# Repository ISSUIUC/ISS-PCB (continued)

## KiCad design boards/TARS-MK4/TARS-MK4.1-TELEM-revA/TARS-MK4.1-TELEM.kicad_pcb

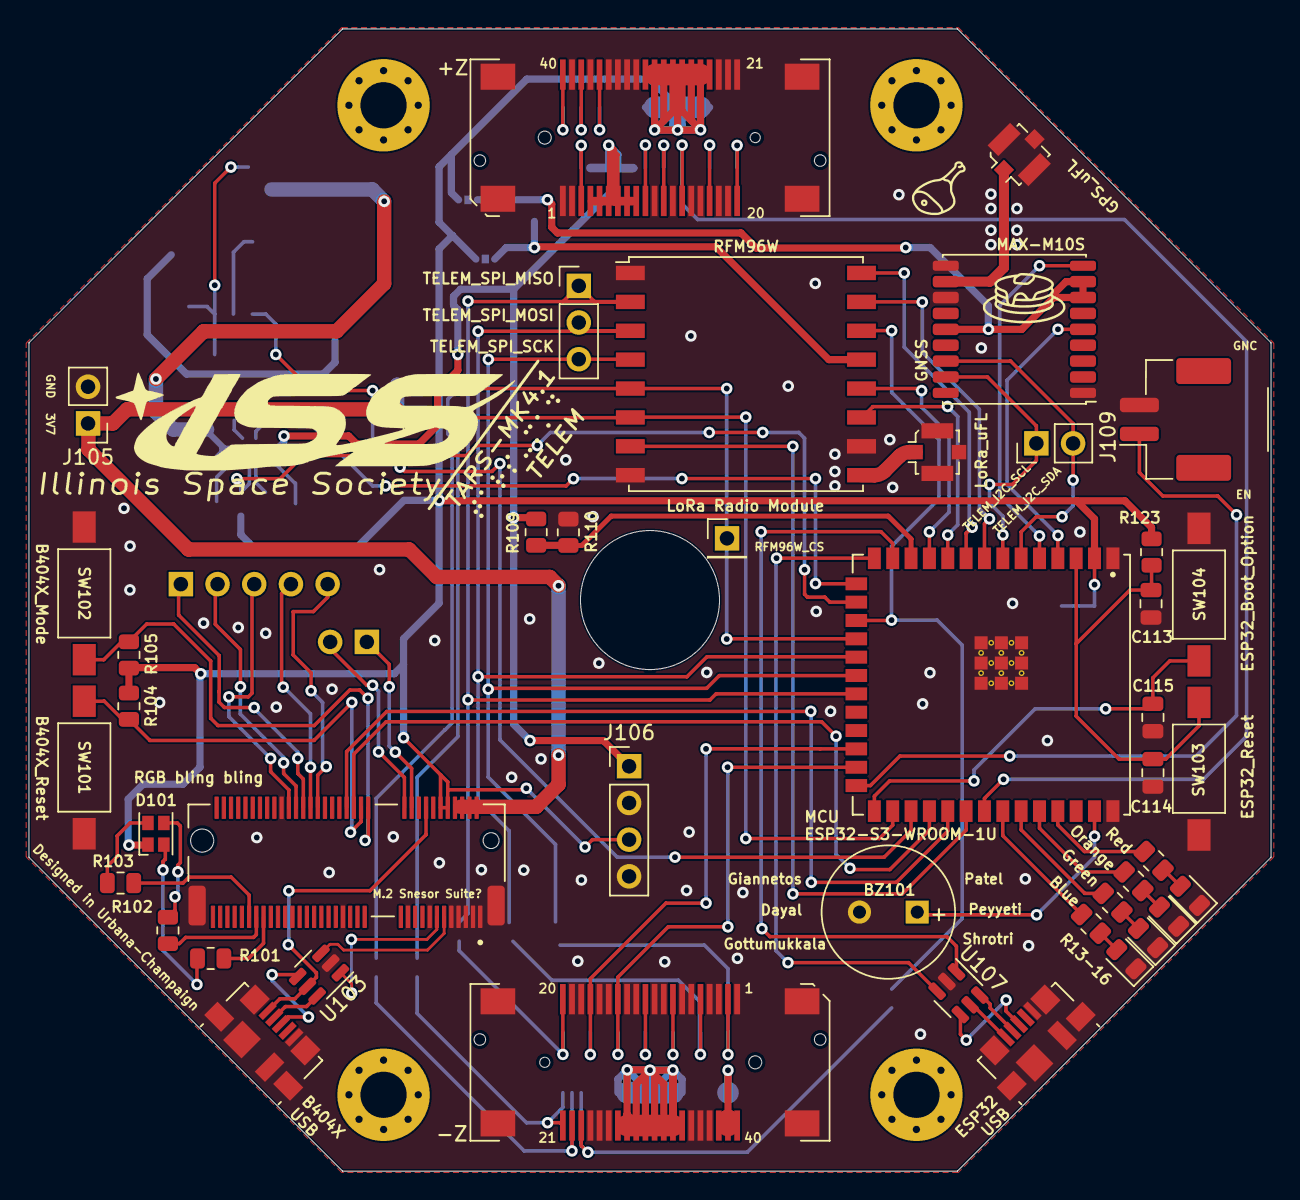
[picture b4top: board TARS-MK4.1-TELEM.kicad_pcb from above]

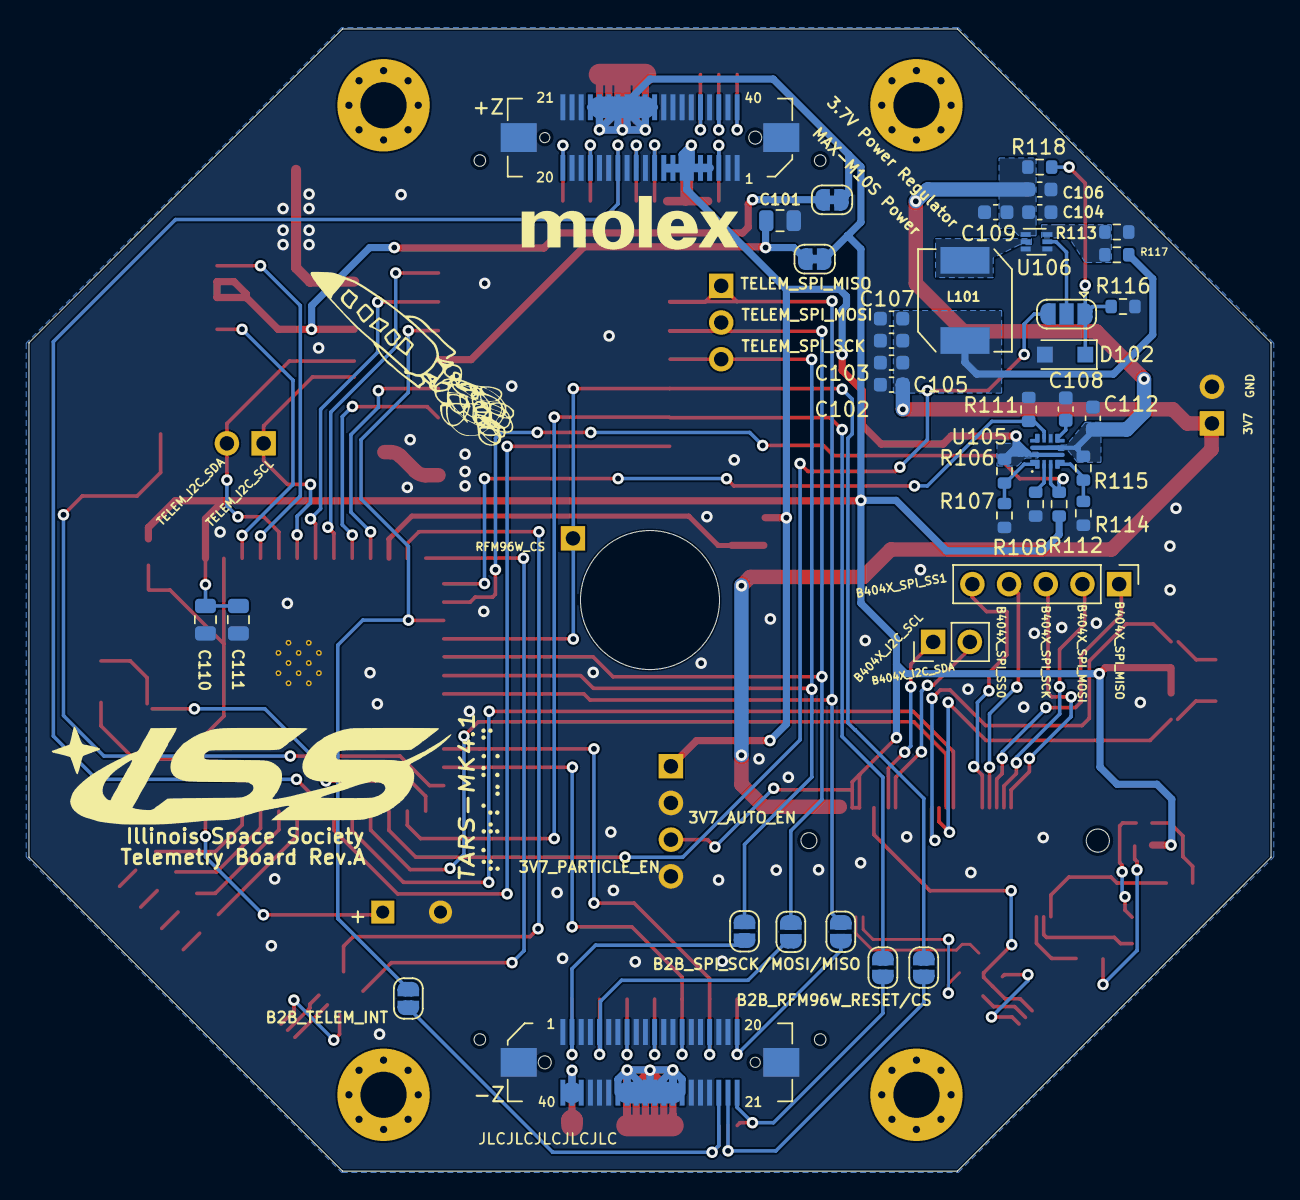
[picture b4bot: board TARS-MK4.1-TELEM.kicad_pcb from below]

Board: 2 copper layers, 86.0 x 79.1 mm, 83 parts (40 on the bottom side), 96 nets.

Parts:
BZ101: Buzzer; MagneticBuzzer_PUI_AT-0927-TT-6-R
C101: 10uF; C_0805_2012Metric
C102, C103, C105, C107: 22uF; C_0603_1608Metric
C104, C106: 10uF; C_0603_1608Metric
C108: 5.1nF; C_0603_1608Metric
C109: 0.1uF; C_0603_1608Metric
C110: 22uF; C_0805_2012Metric
C111, C114, C115: 0.1uF; C_0805_2012Metric
C112: 470uF; C_0603_1608Metric
C113: 1uF; C_0805_2012Metric
D101: LED_ABGR; LED_Cree-PLCC4_2x2mm_CW
D102: BZT52H-A5V1-QX; D_SOD-123F
D103: RED LED; LED_0805_2012Metric
D104: ORANGE LED; LED_0805_2012Metric
D105: GREEN LED; LED_0805_2012Metric
D106: BLUE LED; LED_0805_2012Metric
J101, J104: U.FL; U.FL_Molex_MCRF_73412-0110_Vertical
J102: B404X; TE_21992304
J103, J110: USB_B_Micro; USB_Micro-B_Molex_47346-0001
J105, J108, J114: Conn_01x02; PinHeader_1x02_P2.54mm_Vertical
J106: Conn_01x04; PinHeader_1x04_P2.54mm_Vertical
J107: Conn_01x04; PinHeader_1x05_P2.54mm_Vertical
J109: Molex Micro-Lock 5055780271; Molex_Micro-Lock_5055780271_1x02-1MP_P2.00mm_Horizontal
J111, J112: Molex_SlimStack_2091680401_2x20_P0.635mm; Molex_SlimStack_Receptacle_2091680401_2x20_P0.635mm
J113: Conn_01x03; PinHeader_1x03_P2.54mm_Vertical
J115: Conn_01x05; PinHeader_1x01_P2.54mm_Vertical
J116, J117: Molex_SlimStack_Plug_550910474_2x20_P0.365mm
JP101, JP102, JP103, JP104, JP105, JP108: SolderJumper_2_Open; SolderJumper-2_P1.3mm_Open_RoundedPad1.0x1.5mm
JP106, JP107: Jumper_NC_Small; SolderJumper-2_P1.3mm_Bridged_RoundedPad1.0x1.5mm
JP109: SolderJumper_3_Open; SolderJumper-3_P1.3mm_Open_RoundedPad1.0x1.5mm
L101: 2.2uH; L_TDK_SPM6530
R101, R102, R103: 1K; R_0805_2012Metric
R104, R105: 9K; R_0805_2012Metric
R106, R115: 470k; R_0603_1608Metric
R107, R114: 120k; R_0603_1608Metric
R108: 390k; R_0603_1608Metric
R109: 200k; R_0805_2012Metric
R110: 100k; R_0805_2012Metric
R111: 866; R_0603_1608Metric
R112: 47k; R_0603_1608Metric
R113, R116: 30k; R_0603_1608Metric
R117: 155k; R_0603_1608Metric
R118: 20k; R_0603_1608Metric
R119, R120, R121, R122: 470; R_0805_2012Metric
R123: 10K; R_0805_2012Metric
SW101, SW102, SW103, SW104: SW_Push; SW_SPST_FSMSM
U101: MAX-M10S; ublox_MAX
U102: RFM96W-433S2; HOPERF_RFM9XW_SMD
U103, U107: USBLC6-2SC6Y; SOT-23-6
U104: ESP32-S3-WROOM-1U
U105: TPS25947; VQFN-HR-RPW0010A
U106: TI_TPS566242DRLR; SOT-563

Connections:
/3V3: C110.1, C111.1, D101.1 (A), J102.10, J102.12, J106.3, J111.24, J111.25, J111.26, J111.27, J111.28, J111.29, J111.30, J111.31, J116.24, J116.25, J116.26, J116.27, J116.28, J116.29, J116.30, J116.31, JP106.1 (A), JP107.1 (A), R104.1, R105.1, R112.2, R123.2, U104.2 (3V3)
/3V7: C102.1, C103.1, C105.1, C107.1, J102.2, J102.4, J102.6, J102.8, J105.1, L101.1, R117.2
/3V7_PARTICLE_EN: JP109.3 (B), U104.29 (IO36)
/5V: J112.27, J112.28, J112.29, J112.30, J112.31, J112.32, J112.33, J112.34, J117.27, J117.28, J117.29, J117.30, J117.31, J117.32, J117.33, J117.34
/B2B_I2C_SCL: J112.11, J117.11
/B2B_I2C_SDA: J112.8, J117.8
/B2B_RFM96W_CS: J112.22, J117.22, JP102.1 (A)
/B2B_RFM96W_INT: J112.23, J117.23, JP108.2 (B)
/B2B_RFM96W_RESET: J112.21, J117.21, JP101.1 (A)
/B2B_SERVO_PWM: J111.3, J116.3
/B2B_SPI_MISO: J112.20, J117.20, JP103.1 (A)
/B2B_SPI_MOSI: J112.5, J117.5, JP104.1 (A)
/B2B_SPI_SCK: J112.2, J117.2, JP105.1 (A)
/B2B_UART_RX_PMB: J111.20, J116.20
/B2B_UART_RX_TELEM: J112.17, J117.17, U104.24 (IO47)
/B2B_UART_TX_PMB: J111.17, J116.17
/B2B_UART_TX_TELEM: J112.14, J117.14, U104.25 (IO48)
/B404X_I2C_SCL: J102.20, J108.1
/B404X_I2C_SDA: J102.22, J108.2
/B404X_Mode: J102.32, R105.2, SW102.2
/B404X_Reset: J102.34, R104.2, SW101.2
/B404X_SPI_MISO: J102.50, J107.1
/B404X_SPI_MOSI: J102.52, J107.2
/B404X_SPI_SCK: J102.54, J107.3
/B404X_SPI_SS0: J102.48, J107.4
/B404X_SPI_SS1: J102.46, J107.5
/CHIP_PU: C113.1, C114.2, R123.1, SW103.2, U104.3 (EN)
/ESP_USB_DN: U104.13 (IO19), U107.1 (I/O1)
/ESP_USB_DP: U104.14 (IO20), U107.3 (I/O2)
/GPIO_0: C115.2, SW104.2, U104.27 (IO0)
/ILM_3V7: R111.2, U104.15 (IO3), U105.9 (ILM)
/LED_BLUE: R122.1, U104.34 (IO41)
/LED_GREEN: R121.1, U104.35 (IO42)
/LED_ORANGE: R120.1, U104.36 (RXD0)
/LED_RED: R119.1, U104.37 (TXD0)
/LTE_USB_5V: J102.16, J103.1 (VBUS), U103.5 (VBUS)
/LTE_USB_DN: J102.13, U103.1 (I/O1)
/LTE_USB_DP: J102.11, U103.3 (I/O2)
/MAX-M10S_INT: U101.5 (EXTINT), U104.4 (IO4)
/MAX-M10S_RESET: U101.9 (RESET_N), U104.5 (IO5)
/PG_3V7: R112.1, U104.16 (IO46), U105.3 (PG/AUXOFF)
/PWM_BUZZER: BZ101.1 (-), U104.39 (IO1)
/RESERVED_1: J111.10, J116.10
/RESERVED_2: J111.12, J116.12
/RESERVED_3: J111.36, J116.36
/RESERVED_4: J111.38, J116.38
/RFM96W_CS: J115.1, JP102.2 (B), U102.5 (NSS), U104.18 (IO10)
/RFM96W_DIO1: U102.15 (DIO1), U104.8 (IO15)
/RFM96W_DIO2: U102.16 (DIO2), U104.9 (IO16)
/RFM96W_DIO3: U102.11 (DIO3), U104.10 (IO17)
/RFM96W_DIO4: U102.12 (DIO4), U104.11 (IO18)
/RFM96W_DIO5: U102.7 (DIO5), U104.32 (IO39)
/RFM96W_RESET: JP101.2 (B), U102.6 (RESET), U104.28 (IO35)
/RGB_B: J102.65, R103.1
/RGB_G: J102.63, R102.1
/RGB_R: J102.61, R101.1
/RTL_SDR_EN: J109.1, U104.26 (IO45)
/TEENSY_GPIO_1: J111.40, J116.40
/TEENSY_SWITCH: J111.14, J116.14, U104.33 (IO40)
/TELEM_I2C_SCL: J114.1, U101.17 (SCL), U104.7 (IO7)
/TELEM_I2C_SDA: J114.2, U101.16 (SDA), U104.6 (IO6)
/TELEM_INT: JP108.1 (A), U102.14 (DIO0), U104.17 (IO9)
/TELEM_SPI_MISO: J113.1, JP103.2 (B), U102.2 (MISO), U104.21 (IO13)
/TELEM_SPI_MOSI: J113.2, JP104.2 (B), U102.3 (MOSI), U104.19 (IO11)
/TELEM_SPI_SCK: J113.3, JP105.2 (B), U102.4 (SCK), U104.20 (IO12)
/Teensy_3V3: J112.38, J112.39, J112.40, J117.38, J117.39, J117.40
/UART_RX_PARTICLE: J102.38, U104.31 (IO38)
/UART_TX_PARTICLE: J102.36, U104.30 (IO37)
/VBAT: J106.1, J111.4, J111.5, J111.6, J111.7, J111.8, J111.9, J116.4, J116.5, J116.6, J116.7, J116.8, J116.9, R106.1, R109.1, U105.5 (IN)
/VBAT_3V7: C104.1, C106.1, C109.1, C112.1, R115.2, R118.2, U105.6 (OUT), U106.1 (VIN)
/VBAT_SENSE: R109.2, R110.1, U104.12 (IO8)
GND: BZ101.2 (+), C101.2, C102.2, C103.2, C104.2, C105.2, C106.2, C107.2, C108.2, C109.2, C110.2, C111.2, C112.2, C113.2, C114.1, C115.1, D102.2 (A), D103.1 (K), D104.1 (K), D105.1 (K), D106.1 (K), J101.2 (Ext), J102.1, J102.3, J102.5, J102.7, J102.9, J102.15, J102.21, J102.39, J102.56, J102.S1 (SHIELD), J103.5 (GND), J103.6 (Shield), J104.2 (Ext), J105.2, J106.2, J106.4, J109.2, J110.5 (GND), J110.6 (Shield), J111.1, J111.2, J111.11, J111.13, J111.15, J111.16, J111.18, J111.19, J111.21, J111.22, J111.23, J111.32, J111.33, J111.34, J111.35, J111.37, J111.39, J111.MP (MountPin), J112.1, J112.3, J112.4, J112.6, J112.7, J112.9, J112.10, J112.12, J112.13, J112.15, J112.16, J112.18, J112.19, J112.24, J112.25, J112.26, J112.35, J112.36, J112.37, J112.MP (MountPin), J116.1, J116.2, J116.11, J116.13, J116.15, J116.16, J116.18, J116.19, J116.21, J116.22, J116.23, J116.32, J116.33, J116.34, J116.35, J116.37, J116.39, J116.MP (MountPin), J117.1, J117.3, J117.4, J117.6, J117.7, J117.9, J117.10, J117.12, J117.13, J117.15, J117.16, J117.18, J117.19, J117.24, J117.25, J117.26, J117.35, J117.36, J117.37, J117.MP (MountPin), R107.2, R108.2, R110.2, R111.1, R113.2, R114.2, R116.2, SW101.1, SW102.1, SW103.1, SW104.1, U101.1 (GND), U101.10 (GND), U101.12 (GND), U102.1 (GND), U102.8 (GND), U102.10 (GND), U103.2 (GND), U104.1 (GND), U104.40 (GND), U104.41 (EPAD), U105.8 (GND), U106.3 (GND), U106.4 (AGND), U107.2 (GND)
unnamed: C101.1, JP106.2 (B), U102.13 (3.3V)
unnamed: C108.1, U105.7 (DVDT)
unnamed: D101.2 (BK), R103.2
unnamed: D101.3 (GK), R102.2
unnamed: D101.4 (RK), R101.2
unnamed: D102.1 (K), JP109.1 (A), R116.1, R118.1
unnamed: D103.2 (A), R119.2
unnamed: D104.2 (A), R120.2
unnamed: D105.2 (A), R121.2
unnamed: D106.2 (A), R122.2
unnamed: J101.1 (In), U101.11 (RF_IN)
unnamed: J103.2 (D-), U103.6 (I/O1)
unnamed: J103.3 (D+), U103.4 (I/O2)
unnamed: J104.1 (In), U102.9 (ANT)
unnamed: J110.1 (VBUS), U107.5 (VBUS)
unnamed: J110.2 (D-), U107.6 (I/O1)
unnamed: J110.3 (D+), U107.4 (I/O2)
unnamed: JP107.2 (B), U101.7 (V_IO), U101.8 (VCC), U101.14 (VCC_RF)
unnamed: JP109.2 (C), U106.5 (EN)
unnamed: L101.2, U106.2 (SW)
unnamed: R106.2, R107.1, U105.1 (EN/UVLO)
unnamed: R108.1, U105.2 (OVLO/OVCSEL)
unnamed: R113.1, R117.1, U106.6 (FB)
unnamed: R114.1, R115.1, U105.4 (PGTH/NFLT)

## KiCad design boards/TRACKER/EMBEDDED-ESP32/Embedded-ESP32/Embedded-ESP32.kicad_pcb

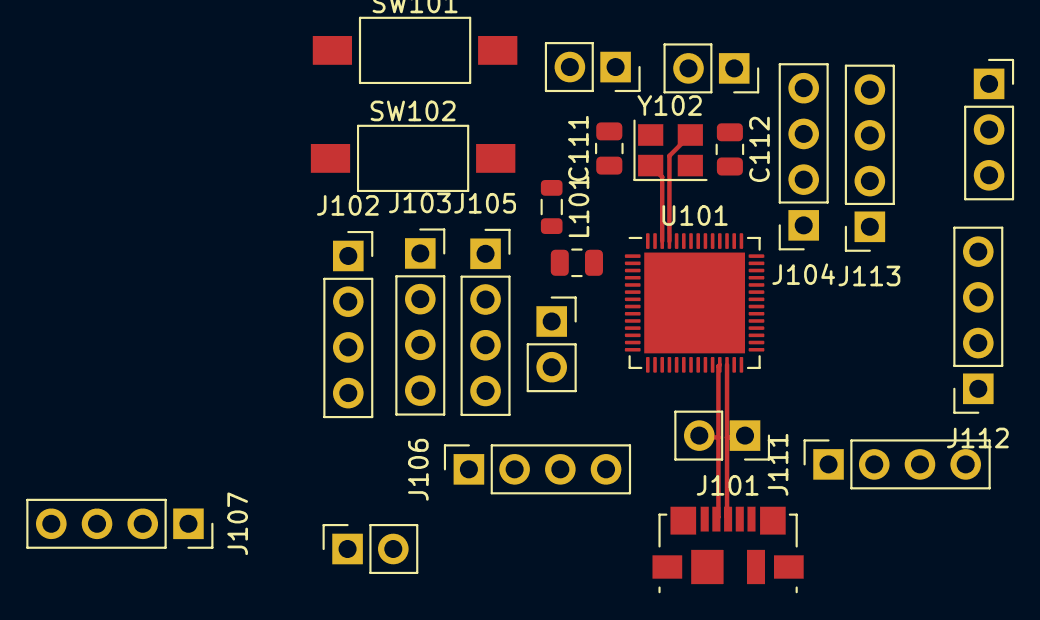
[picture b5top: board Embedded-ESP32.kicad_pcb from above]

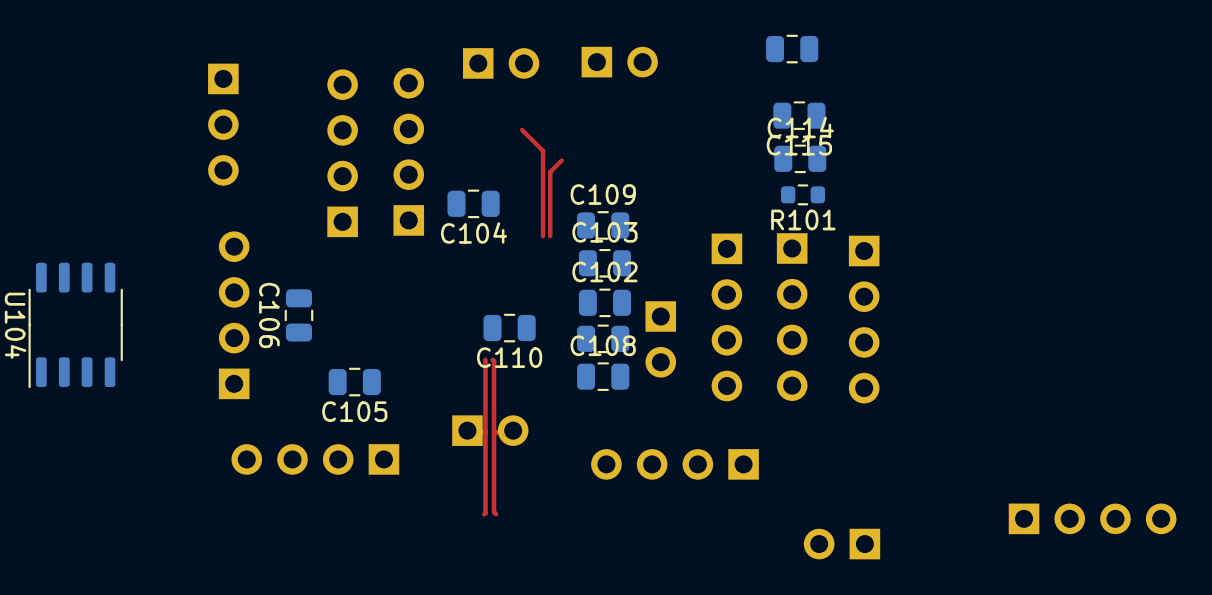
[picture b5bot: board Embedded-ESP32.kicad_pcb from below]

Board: 2 copper layers, 38 parts (14 on the bottom side), 53 nets.

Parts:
C101, C115: 1uF; C_0805_2012Metric
C102: 10nF; C_0805_2012Metric
C103, C104, C105, C106, C107, C108, C113, C114: 0.1uF; C_0805_2012Metric
C109, C110: 10uF; C_0805_2012Metric
C111, C112: TBD; C_0805_2012Metric
J101: USB_B_Micro; USB_Micro-B_Molex_47346-0001
J102, J103, J104, J105, J106, J107, J111, J112, J113: Conn_01x04; PinSocket_1x04_P2.54mm_Vertical
J108: Conn_01x03; PinSocket_1x03_P2.54mm_Vertical
J109, J110, J114, J115, J116: Conn_01x02; PinSocket_1x02_P2.54mm_Vertical
L101: L; L_0805_2012Metric
R101: 10K; R_0603_1608Metric
SW101, SW102: SW_Push; SW_SPST_FSMSM
U101: ESP32-S3; QFN-56-1EP_7x7mm_P0.4mm_EP5.6x5.6mm
U104: MX25L3233FM1; SOP-8_3.9x4.9mm_P1.27mm
Y102: Crystal_GND24; Crystal_SMD_Abracon_ABM8G-4Pin_3.2x2.5mm

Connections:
+3V3: C101.1, C102.1, C103.1, C104.1, C108.1, C109.1, C110.1, J116.2, L101.1, U101.20 (VDD3P3_RTC), U101.46 (VDD3P3_CPU), U101.55 (VDDA), U101.56 (VDDA)
/CHIP_PU: C114.2, C115.1, R101.1, SW102.2, U101.4 (CHIP_PU/RESET)
/CS: J111.4, U101.32 (SPICS0/GPIO29), U104.1 (~CS)
/GPIO_0: C113.2, J103.1, SW101.2, U101.5 (GPIO0/BOOT)
/HOLD: J111.2, U101.30 (SPIHD/GPIO27), U104.7 (~HOLD/SIO3)
/SCK: J112.1, U101.33 (SPICLK/GPIO30), U104.6 (SCLK)
/SPID: J112.3, U101.35 (SPID/GPIO32), U104.5 (SI/SIO0)
/SPIQ: J112.2, U101.34 (SPIQ/GPIO31), U104.2 (SO/SIO1)
/VDD_SPI: C105.1, C106.1, U101.29 (VDD_SPI), U104.8 (VCC)
/WP: J111.3, U101.31 (SPIWP/GPIO28), U104.3 (~WP/SIO2)
/X1: C111.1, U101.54 (XTAL_P), Y102.1
/X2: C112.1, U101.53 (XTAL_N), Y102.3
GND: C101.2, C102.2, C103.2, C104.2, C105.2, C106.2, C107.2, C108.2, C109.2, C110.2, C111.2, C112.2, C113.1, C114.1, C115.2, J101.5 (GND), J101.6 (Shield), J115.2, J116.1, SW101.1, SW102.1, U101.57 (GND), U104.4 (GND), Y102.2, Y102.4
unnamed: J101.3 (D+), J114.1, U101.26 (GPIO20/USB_D+/ADC2_CH9)
unnamed: J101.2 (D-), J114.2, U101.25 (GPIO19/USB_D-/ADC2_CH8)
unnamed: J102.1, U101.9 (GPIO4/ADC1_CH3)
unnamed: J102.2, U101.10 (GPIO5/ADC1_CH4)
unnamed: J102.3, U101.11 (GPIO6/ADC1_CH5)
unnamed: J102.4, U101.12 (GPIO7/ADC1_CH6)
unnamed: J103.2, U101.6 (GPIO1/ADC1_CH0)
unnamed: J103.3, U101.7 (GPIO2/ADC1_CH1)
unnamed: J103.4, U101.8 (GPIO3/ADC1_CH2)
unnamed: J104.1, U101.44 (MTCK/JTAG/GPIO39)
unnamed: J104.2, U101.45 (MTDO/JTAG/GPIO40)
unnamed: J104.3, U101.47 (MTDI/JTAG/GPIO41)
unnamed: J104.4, U101.48 (MTMS/JTAG/GPIO42)
unnamed: J105.1, U101.13 (GPIO8/ADC1_CH7)
unnamed: J105.2, U101.14 (GPIO9/ADC1_CH8)
unnamed: J105.3, U101.15 (GPIO10/ADC1_CH9)
unnamed: J105.4, U101.16 (GPIO11/ADC2_CH0)
unnamed: J106.1, U101.17 (GPIO12/ADC2_CH1)
unnamed: J106.2, U101.18 (GPIO13/ADC2_CH2)
unnamed: J106.3, U101.19 (GPIO14/ADC2_CH3)
unnamed: J106.4, U101.23 (GPIO17/ADC2_CH6)
unnamed: J107.1, U101.24 (GPIO18/ADC2_CH7)
unnamed: J107.2, U101.27 (GPIO21)
unnamed: J107.3, U101.43 (GPIO38)
unnamed: J107.4, U101.51 (GPIO45)
unnamed: J108.1, U101.52 (GPIO46)
unnamed: J108.2, U101.37 (SPICLK_P/GPIO47)
unnamed: J108.3, U101.36 (SPICLK_N/GPIO48)
unnamed: J109.1, U101.49 (U0TXD/PROG/GPIO43)
unnamed: J109.2, U101.50 (U0RXD/PROG/GPIO44)
unnamed: J110.1, U101.21 (GPIO15/ADC2_CH4/XTAL_32K_P)
unnamed: J110.2, U101.22 (GPIO16/ADC2_CH5/XTAL_32K_N)
unnamed: J111.1, U101.28 (SPI_CS1/GPIO26)
unnamed: J112.4, U101.38 (GPIO33)
unnamed: J113.1, U101.39 (GPIO34)
unnamed: J113.2, U101.40 (GPIO35)
unnamed: J113.3, U101.41 (GPIO36)
unnamed: J113.4, U101.42 (GPIO37)
unnamed: J115.1, U101.1 (LNA_IN/RF)
VDD3P3: C107.1, L101.2, U101.2 (VDD3P3), U101.3 (VDD3P3)

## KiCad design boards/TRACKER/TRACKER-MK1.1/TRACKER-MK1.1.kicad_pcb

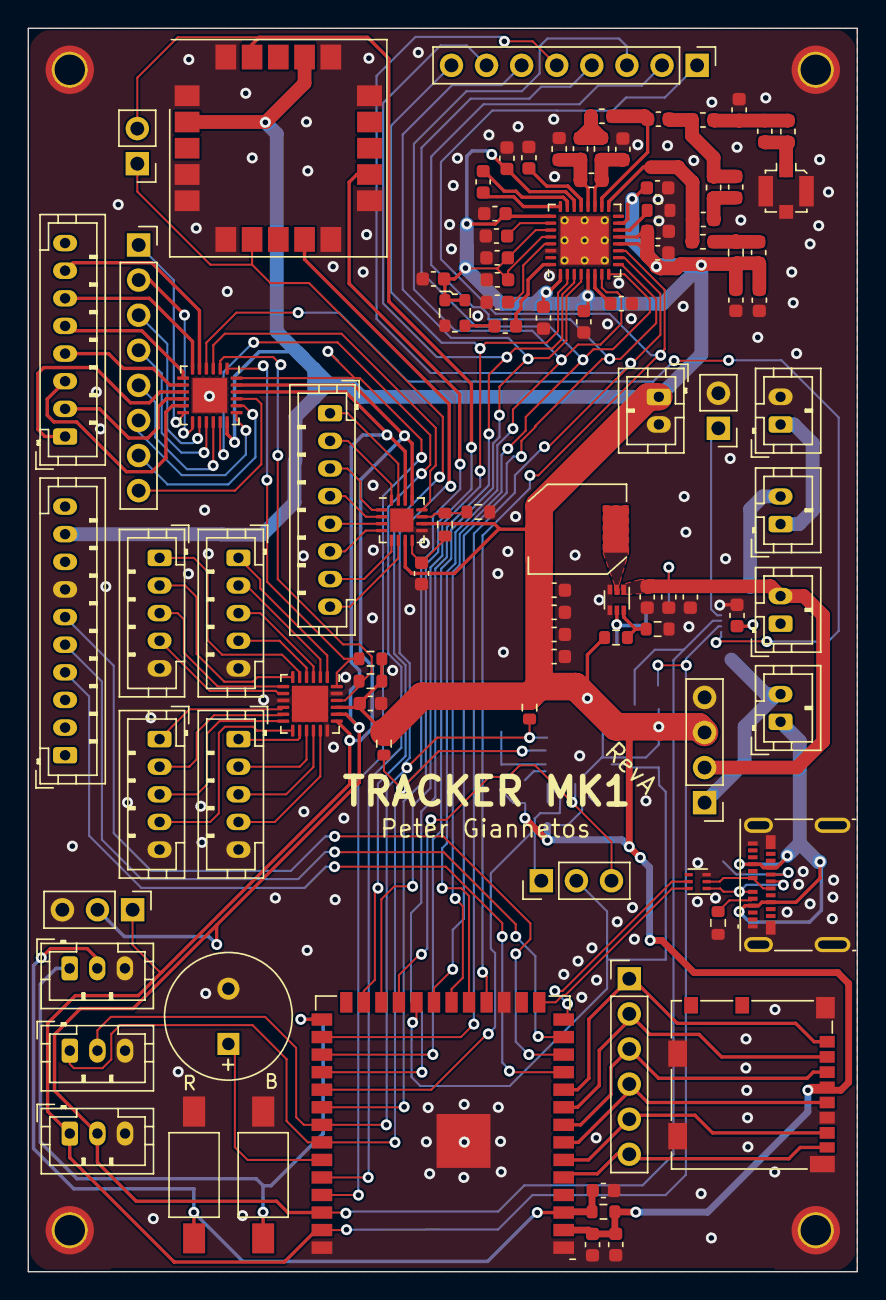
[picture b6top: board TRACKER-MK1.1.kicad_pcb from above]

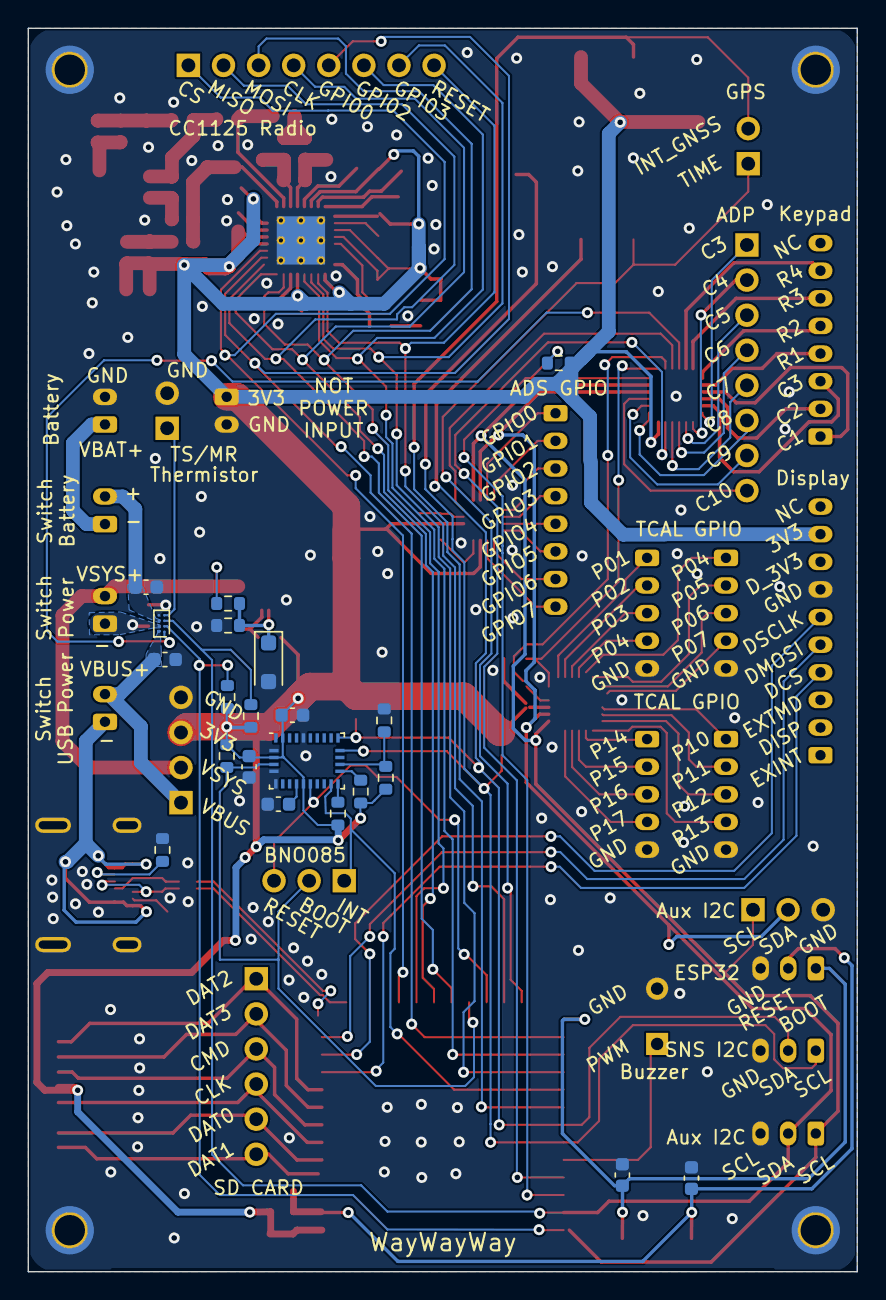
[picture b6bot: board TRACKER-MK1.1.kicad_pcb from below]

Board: 2 copper layers, 60.0 x 90.0 mm, 123 parts (21 on the bottom side), 117 nets.

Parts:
BT101: Battery; JST_PH_B2B-PH-K_1x02_P2.00mm_Vertical
BZ101: Buzzer; MagneticBuzzer_PUI_AT-0927-TT-6-R
C101, C103, C105, C118: 1uF; C_0603_1608Metric
C102, C108, C112, C115, C116, C117, C119, C120: 0.1uF; C_0603_1608Metric
C104, C106, C107: 10uF; C_0603_1608Metric
C109, C110, C111, C113, C114: 22uF; C_0603_1608Metric
C201: 100nF; C_0603_1608Metric
C202: 22pF; C_0603_1608Metric
C203: 1.8nF; C_0603_1608Metric
C204, C217: 10nF; C_0603_1608Metric
C205: 33pF; C_0603_1608Metric
C206: 100pF; C_0603_1608Metric
C207: 15pF; C_0603_1608Metric
C208, C210, C211, C214, C215, C218, C219, C220, C223, C224, C226: 47nF; C_0603_1608Metric
C209: 220nF; C_0603_1608Metric
C212, C222: 3.3pF; C_0603_1608Metric
C213: 1pF; C_0603_1608Metric
C216: 2.2pF; C_0603_1608Metric
C221: 3pF; C_0603_1608Metric
C225: TBD; C_0603_1608Metric
D101: BZT52H-A5V1-QX; D_SOD-123F
H101, H102, H103, H104: MountingHole_2.2mm_M2_ISO7380_Pad_TopBottom
J101: 1054500101; USB_C_Receptacle_Molex_105450-0101
J102: 1040310811; microSD_HC_Molex_104031-0811
J103, J104, J105, J106: JST-PH; JST_PH_B5B-PH-K_1x05_P2.00mm_Vertical
J107: JST-PH; JST_PH_B10B-PH-K_1x10_P2.00mm_Vertical
J108, J109: JST-PH; JST_PH_B8B-PH-K_1x08_P2.00mm_Vertical
J111: 2.54mm Pin Header; PinSocket_1x08_P2.54mm_Vertical
J112, J114, J115: JST-PH; JST_PH_B3B-PH-K_1x03_P2.00mm_Vertical
J113: JST-PH; JST_PH_B2B-PH-K_1x02_P2.00mm_Vertical
J116: U.FL; U.FL_Molex_MCRF_73412-0110_Vertical
J117: 2.54mm Pin Header; PinHeader_1x06_P2.54mm_Vertical
J120, J123: 2.54mm Pin Header; PinHeader_1x03_P2.54mm_Vertical
J121: 2.54mm Pin Header; PinHeader_1x02_P2.54mm_Vertical
J125: 2.54mm Pin Header; PinHeader_1x04_P2.54mm_Vertical
J126: 2.54mm Pin Header; PinHeader_1x08_P2.54mm_Vertical
L101: 2.2uH; L_TDK_SPM6530
L201: 10nH; L_0603_1608Metric
L202, L205, L207, L208: 12nH; L_0603_1608Metric
L203: 7.5nH; L_0603_1608Metric
L204: 15nH; L_0603_1608Metric
L206: 18nH; L_0603_1608Metric
R101, R102, R107, R114: 10k; R_0603_1608Metric
R103, R104: 5.1k; R_0603_1608Metric
R105: 100k; R_0603_1608Metric
R106, R112, R113: 0; R_0603_1608Metric
R108: 20k; R_0603_1608Metric
R109, R110: 30k; R_0603_1608Metric
R111: 135k; R_0603_1608Metric
R115, R116: 2.2k; R_0603_1608Metric
R117: 10K; R_0603_1608Metric
R118, R119, R120, R121: 3.3k; R_0603_1608Metric
R201: 56k; R_0603_1608Metric
R202: 10; R_0603_1608Metric
SW101: VBUS Switch; JST_PH_B2B-PH-K_1x02_P2.00mm_Vertical
SW102: Battery Switch; JST_PH_B2B-PH-K_1x02_P2.00mm_Vertical
SW103: Power Switch; JST_PH_B2B-PH-K_1x02_P2.00mm_Vertical
SW104, SW105: SW_Push; SW_SPST_FSMSM
TH101: B3950 NTC; PinHeader_1x02_P2.54mm_Vertical
U101: TCAL9539-Q1; WQFN-24-1EP_4x4mm_P0.5mm_EP2.6x2.6mm
U102: BQ25180; Texas_DSBGA-8_0.705x1.468mm_Layout2x4_P0.4mm
U103: ECMF02-2AMX6; ST_UQFN-6L_1.5x1.7mm_P0.5mm
U104: ADS7138-Q1; WQFN-16-1EP_3x3mm_P0.5mm_EP1.68x1.68mm
U105: ADP5589; LFCSP-24-1EP_4x4mm_P0.5mm_EP2.5x2.5mm
U106: TPS566242DRLR; SOT-563
U107: ESP32-S3-WROOM-1
U108: BNO085; LGA-28_5.2x3.8mm_P0.5mm
U109: SAM-M10Q-00B; uBlox_SAM-M10Q
U201: CC1125; VQFN-32-1EP_5x5mm_P0.5mm_EP3.5x3.5mm_ThermalVias
X201: ECS-TXO-2016MV-400-TR; Oscillator_SMD_ECS_2520MV-xxx-xx-4Pin_2.5x2.0mm

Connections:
/3V3: C102.1, C109.1, C110.1, C111.1, C112.1, C113.1, C114.1, C119.1, C120.1, C201.1, C204.1, C205.2, C206.1, C208.1, C211.1, C214.1, C215.1, C219.1, C220.1, C223.1, C224.1, C226.1, J102.4 (VDD), J107.9, J113.1, J125.3, L101.2, R101.1, R102.1, R107.1, R111.1, R112.2, R114.2, R115.2, R116.2, R117.2, R118.1, R119.1, R120.1, R121.1, R202.2, U101.21 (VCC), U104.7 (AVDD), U104.10 (DVDD), U105.18 (VDD), U107.2 (3V3), U108.3 (VDD), U108.10 (CLKSEL0), U108.28 (VDDIO), U109.2 (V_IO), U109.17 (VCC), U201.1 (VDD_GUARD), U201.5 (DVDD), U201.12 (DVDD), U201.13 (AVDD_IF), U201.15 (AVDD_RF), U201.22 (AVDD_SYNTH1), U201.25 (AVDD_PFD_CHP), U201.27 (AVDD_SYNTH2), U201.28 (AVDD_XOSC), X201.1 (Tri-State), X201.4 (VDD)
/ DISPLAY_CS: J107.4, U107.11 (IO18)
/ DISPLAY_MOSI: J107.5, U107.13 (IO19)
/ DISPLAY_SCLK: J107.6, U107.12 (IO8)
/ADC1_ALERT: U104.12 (ALERT), U105.3 (R5)
/ADC_DECAP: C105.1, R105.1, U104.8 (DECAP)
/ADP_~INT: R107.2, U105.24 (~INT), U107.37 (TXD0)
/ADP_~RESET: U105.17 (~RST), U107.36 (RXD0)
/BNO085_BOOT: J120.2, R114.1, U107.22 (IO14), U108.4 (BOOTN)
/BNO085_RESET: J120.3, U107.23 (IO21), U108.11 (NRST)
/BQ25180_INT: U102.A1 (INT), U105.4 (R4)
/CC1125_GPIO0: J126.5, U107.28 (IO35), U201.10 (GPIO0)
/CC1125_GPIO2: J126.6, U107.29 (IO36), U201.4 (GPIO2)
/CC1125_GPIO3: J126.7, U107.30 (IO37), U201.3 (GPIO3)
/CC1125_~RESET: J126.8, U107.24 (IO47), U201.2 (~RESET)
/CHIP_PU: C116.2, C118.1, J112.2, R117.1, SW105.2, U107.3 (EN)
/DN: J101.A7 (D-), J101.B7 (D-), U103.2 (D-_in)
/DP: J101.A6 (D+), J101.B6 (D+), U103.1 (D+_in)
/GPIO_0: C115.2, J112.1, SW104.2, U107.27 (IO0)
/I2C_AUX_SCL: J115.1, J123.1, R120.2, U101.19 (SCL), U102.B1 (SCL), U104.13 (SCL), U105.23 (SCL), U107.39 (IO1)
/I2C_AUX_SDA: J115.2, J123.2, R121.2, U101.20 (SDA), U102.C1 (SDA), U104.14 (SDA), U105.22 (SDA), U107.38 (IO2)
/I2C_SNS_SCL: J114.1, R119.2, U107.34 (IO41), U108.19 (H_SCL/SCK/RX), U109.12 (SCL)
/I2C_SNS_SDA: J114.2, R118.2, U107.33 (IO40), U108.20 (H_SDA/H_MISO/TX), U109.9 (SDA)
/INT_BNO085: J120.1, U107.31 (IO38), U108.14 (H_INTN)
/INT_GNSS: J121.2, U107.32 (IO39), U109.19 (EXTINT)
/KEYPAD_C1: J108.1, U105.9 (C0)
/KEYPAD_C2: J108.2, U105.10 (C1)
/KEYPAD_C3: J108.3, U105.11 (C2)
/KEYPAD_R1: J108.4, U105.8 (R0)
/KEYPAD_R2: J108.5, U105.7 (R1)
/KEYPAD_R3: J108.6, U105.6 (R2)
/KEYPAD_R4: J108.7, U105.5 (R3)
/PWM_BUZZER: BZ101.1 (-), U107.35 (IO42)
/Radio/ANT: C225.2, J116.1 (In), L208.2
/SD_CLK: J102.5 (CLK), J117.4, U107.7 (IO7)
/SD_CMD: J102.3 (CMD), J117.3, U107.8 (IO15)
/SD_DAT0: J102.7 (DAT0), J117.5, U107.6 (IO6)
/SD_DAT1: J102.8 (DAT1), J117.6, U107.5 (IO5)
/SD_DAT2: J102.1 (DAT2), J117.1, U107.10 (IO17)
/SD_DAT3: J102.2 (DAT3/CD), J117.2, U107.9 (IO16)
/SPI2_CC1125_~CS: J126.1, U107.18 (IO10), U201.11 (~CS)
/SPI2_RADIO_CLK: J126.4, U107.20 (IO12), U201.8 (SCLK)
/SPI2_RADIO_MISO: J126.2, U107.21 (IO13), U201.9 (SO(GPIO1))
/SPI2_RADIO_MOSI: J126.3, U107.19 (IO11), U201.7 (SI)
/TCAL_INT: R101.2, U101.22 (~INT), U105.2 (R6)
/TCAL_RESET: R102.2, U101.24 (~RESET), U105.1 (R7)
/TIME: J121.1, U107.25 (IO48), U109.7 (TIMEPULSE)
/TS/MR: TH101.1, U102.D1 (TS/MR)
/USB_ESP_DN: U103.5 (D-_out), U107.14 (IO20)
/USB_ESP_DP: U103.6 (D+_out), U107.15 (IO3)
/VBAT: C103.1, SW102.2 (B), U102.C2 (BAT)
/VBUS: C101.1, J125.1, SW101.2 (B), U102.A2 (IN)
/VSYS: C106.1, C107.1, C108.1, J125.2, R108.2, SW103.2 (B), U106.1 (VIN)
GND: BT101.2 (-), BZ101.2 (+), C101.2, C102.2, C103.2, C104.1, C105.2, C106.2, C107.2, C108.2, C109.2, C110.2, C111.2, C112.2, C113.2, C114.2, C115.1, C116.1, C117.2, C118.2, C119.2, C120.2, C201.2, C204.2, C206.2, C208.2, C209.2, C210.2, C211.2, C214.2, C215.2, C217.2, C218.2, C219.2, C220.2, C221.1, C222.1, C223.2, C224.2, C226.2, D101.2 (A), H101.1, H102.1, H103.1, H104.1, J101.A1 (GND), J101.A12 (GND), J101.B1 (GND), J101.B12 (GND), J101.S1 (SHIELD), J102.6 (VSS), J102.11 (SHIELD), J103.5, J104.5, J105.5, J106.5, J107.7, J112.3, J113.2, J114.3, J115.3, J116.2 (Ext), J123.3, J125.4, L202.1, R103.2, R104.2, R106.2, R109.2, R110.2, R113.1, R201.1, SW104.1, SW105.1, TH101.2, U101.9 (GND), U101.18 (A0), U101.23 (A1), U101.25 (GND), U102.D2 (GND), U103.3 (GND), U104.9 (GND), U104.17 (EPAD), U105.25 (GND), U106.3 (GND), U106.4 (AGND), U107.1 (GND), U107.17 (IO9), U107.40 (GND), U107.41 (EPAD), U108.2 (GND), U108.5 (PS1), U108.6 (PS0/WAKE), U108.25 (GNDIO), U109.1 (GND), U109.4 (GND), U109.5 (GND), U109.6 (GND), U109.10 (GND), U109.11 (GND), U109.15 (GND), U109.16 (GND), U109.20 (GND), U201.30 (XOSC_Q1), U201.33 (GND_EP), X201.2 (GND)
unnamed: BT101.1 (+), SW102.1 (A)
unnamed: C205.1, L201.2, R202.1
unnamed: C207.2, C213.1, L203.1
unnamed: C212.1, L205.2, L207.1
unnamed: C213.2, C216.1, L203.2, L206.1
unnamed: C221.2, C225.1, L206.2, L208.1
unnamed: D101.1 (K), R108.1, R109.1, U106.5 (EN)
unnamed: J101.A5 (CC1), R103.1
unnamed: J101.B5 (CC2), R104.1
unnamed: J103.1, U101.14
unnamed: J103.2, U101.15
unnamed: J103.3, U101.16
unnamed: J103.4, U101.17
unnamed: J104.1, U101.10
unnamed: J104.2, U101.11
unnamed: J104.3, U101.12
unnamed: J104.4, U101.13
unnamed: J105.1, U101.5 (P04)
unnamed: J105.2, U101.6 (P05)
unnamed: J105.3, U101.7 (P06)
unnamed: J105.4, U101.8 (P07)
unnamed: J106.1, U101.1 (P00)
unnamed: J106.2, U101.2 (P01)
unnamed: J106.3, U101.3 (P02)
unnamed: J106.4, U101.4 (P03)
unnamed: J109.1, U104.15 (AIN0/GPIO0)
unnamed: J109.2, U104.16 (AIN1/GPIO1)
unnamed: J109.3, U104.1 (ANI2/GPIO2)
unnamed: J109.4, U104.2 (AIN3/GPIO3)
unnamed: J109.5, U104.3 (AIN4/GPIO4)
unnamed: J109.6, U104.4 (AIN5/GPIO5)
unnamed: J109.7, U104.5 (AIN6/GPIO6)
unnamed: J109.8, U104.6 (AIN7/GPIO7)
unnamed: J111.1, U105.12 (C3)
unnamed: J111.2, U105.13 (C4)
unnamed: J111.3, U105.14 (C5)
unnamed: J111.4, U105.15 (C6)
unnamed: J111.5, U105.16 (C7)
unnamed: J111.6, U105.19 (C8)
unnamed: J111.7, U105.20 (C9)
unnamed: J111.8, U105.21 (C10)
unnamed: J101.A4 (VBUS), J101.A9 (VBUS), J101.B4 (VBUS), J101.B9 (VBUS), SW101.1 (A)
unnamed: C104.2, SW103.1 (A), U102.B2 (SYS)
unnamed: R105.2, R106.1, U104.11 (ADDR)
unnamed: R110.1, R111.2, U106.6 (FB)
unnamed: L101.1, U106.2 (SW)
unnamed: C117.1, U108.9 (CAP)
unnamed: R116.1, U108.15 (ENV_SCL)
unnamed: R115.1, U108.16 (ENV_SDA)
unnamed: R112.1, R113.2, U108.17 (H_SA0_MOSI)
unnamed: C209.1, U201.6 (DCPL)
unnamed: C210.1, U201.26 (DCPL_PFD_CHP)
unnamed: C217.1, U201.21 (DCPL_VCO)
unnamed: C218.1, U201.29 (DCPL_XOSC)
unnamed: C202.1, U201.32 (EXT_XOSC)
unnamed: C212.2, L202.2, L204.1, U201.20 (LNA_N)
unnamed: C222.2, L204.2, L207.2, U201.19 (LNA_P)
unnamed: C203.2, U201.23 (LPF0)
unnamed: C203.1, U201.24 (LPF1)
unnamed: C207.1, L201.1, U201.17 (PA)
unnamed: R201.2, U201.14 (RBIAS)
unnamed: C216.2, L205.1, U201.18 (TRX_SW)
unnamed: C202.2, X201.3 (OUT)

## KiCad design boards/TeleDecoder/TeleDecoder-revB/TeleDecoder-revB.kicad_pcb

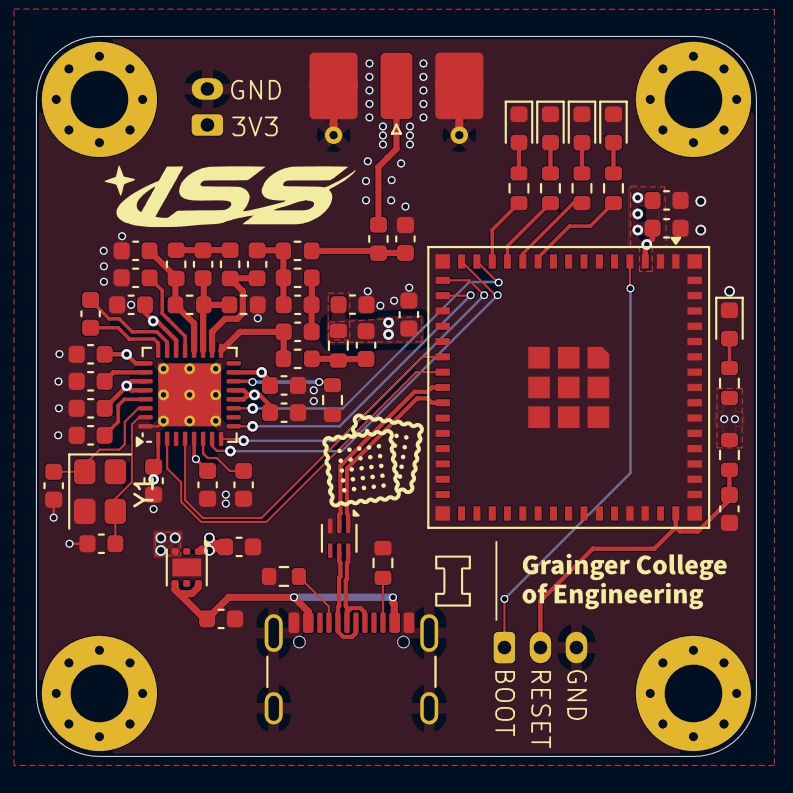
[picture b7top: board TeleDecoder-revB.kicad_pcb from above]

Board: 4 copper layers, 40.0 x 40.0 mm, 64 parts (0 on the bottom side), 45 nets.

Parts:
C1, C2, C127: 1uF; C_0603_1608Metric
C101: 22uF; C_0603_1608Metric
C102: 100nF; C_0603_1608Metric
C103, C119: 10nF; C_0603_1608Metric
C104: 56pF; C_0603_1608Metric
C105: 100pF; C_0603_1608Metric
C106: 39pF; C_0603_1608Metric
C107: 2.2pF; C_0603_1608Metric
C108, C109: 10pF; C_0603_1608Metric
C110, C111, C113: 5.1pF; C_0603_1608Metric
C112: 1.8nF; C_0603_1608Metric
C114: 6.2pF; C_0603_1608Metric
C115, C117, C118, C120, C121, C122, C123, C124, C125: 47nF; C_0603_1608Metric
C116: 220nF; C_0603_1608Metric
D101, D105: LED_RED; LED_0603_1608Metric
D102: LED_BLUE; LED_0603_1608Metric
D103: LED_GREEN; LED_0603_1608Metric
D104: LED_ORANGE; LED_0603_1608Metric
H101, H102, H103, H104: MountingHole; MountingHole_3.2mm_M3_Pad_Via
J101: Conn_01x03; JST_PH_B3B-PH-K_1x03_P2.00mm_Vertical
J102: USB4105-GF-A; USB_C_Receptacle_GCT_USB4105-xx-A_16P_TopMnt_Horizontal
J103: Conn_01x02; JST_PH_B2B-PH-K_1x02_P2.00mm_Vertical
J104: Conn_Coaxial; SMA_Molex_73251-2120_EdgeMount_Horizontal
L101, L102: 56nH; L_0603_1608Metric
L103, L106: 15nH; L_0603_1608Metric
L104, L105: 27nH; L_0603_1608Metric
L107: 43nH; L_0603_1608Metric
L108: 22nH; L_0603_1608Metric
R101, R102: 5.1k; R_0603_1608Metric
R103: 18; R_0603_1608Metric
R104: 56k; R_0603_1608Metric
R105, R106, R107, R108, R110: 470; R_0603_1608Metric
R109: 20k; R_0603_1608Metric
U101: ESP32-S3-MINI-1U; ESP32-S2-MINI-1U
U102: ECMF02-2AMX6; ST_UQFN-6L_1.5x1.7mm_P0.5mm
U103: CC1120; VQFN-32-1EP_5x5mm_P0.5mm_EP3.5x3.5mm_ThermalVias
U104: TPS746-Q1; WSON-6-1EP_2x2mm_P0.65mm_EP1x1.6mm
Y1: NDK NX3225SA; Crystal_SMD_3225-4Pin_3.2x2.5mm

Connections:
+3V3: C2.1, C101.1, C102.1, C103.1, C104.2, C105.1, C115.1, C117.1, C118.1, C120.1, C121.1, C123.1, C124.1, J103.1, R103.2, R109.2, R110.1, U101.3 (3V3), U103.1 (VDD_GUARD), U103.5 (DVDD), U103.12 (DVDD), U103.13 (AVDD_IF), U103.15 (AVDD_RF), U103.22 (AVDD_SYNTH1), U103.25 (AVDD_PFD_CHP), U103.27 (AVDD_SYNTH2), U103.28 (AVDD_XOSC), U104.1 (OUT)
+5V: C1.1, J102.A4 (VBUS), J102.A9 (VBUS), J102.B4 (VBUS), J102.B9 (VBUS), U104.4 (EN), U104.6 (IN)
/BOOT: J101.1, U101.4 (IO0)
/CS_RADIO: U101.14 (IO10), U103.11 (~CS)
/D+: J102.A6 (D+), J102.B6 (D+), U102.6 (D+_out)
/D-: J102.A7 (D-), J102.B7 (D-), U102.5 (D-_out)
/LED_BLUE: R106.1, U101.13 (IO9)
/LED_GREEN: R107.1, U101.12 (IO8)
/LED_ORANGE: R108.1, U101.11 (IO7)
/LED_RED: R105.1, U101.10 (IO6)
/LNA_N: C111.1, L102.2, L105.1, U103.20 (LNA_N)
/LNA_P: C110.1, L102.1, L104.1, U103.19 (LNA_P)
/MISO0: U101.17 (IO13), U103.9 (SO(GPIO1))
/MOSI0: U101.15 (IO11), U103.7 (SI)
/PA: C106.1, L101.1, U103.17 (PA)
/RADIO_INT: U101.21 (IO17), U103.4 (GPIO2)
/RESET: C127.1, J101.2, R109.1, U101.45 (EN)
/RESET_IN: U101.22 (IO18), U103.2 (~RESET)
/SCLK0: U101.16 (IO12), U103.8 (SCLK)
/TRX_SW: C113.1, L106.1, U103.18 (TRX_SW)
/USB_D+: U101.24 (USB_D+), U102.1 (D+_in)
/USB_D-: U101.23 (USB_D-), U102.2 (D-_in)
GND: C1.2, C2.2, C101.2, C102.2, C103.2, C105.2, C108.2, C109.2, C111.2, C114.2, C115.2, C116.2, C117.2, C118.2, C119.2, C120.2, C121.2, C122.2, C123.2, C124.2, C125.2, C127.2, D101.1 (K), D102.1 (K), D103.1 (K), D104.1 (K), D105.1 (K), J101.3, J102.A1 (GND), J102.A12 (GND), J102.B1 (GND), J102.B12 (GND), J102.S1 (SHIELD), J103.2, J104.2 (Ext), L104.2, R101.2, R102.2, R104.2, U101.1 (GND), U101.2 (GND), U101.42 (GND), U101.43 (GND), U101.46 (GND), U101.47 (GND), U101.48 (GND), U101.49 (GND), U101.50 (GND), U101.51 (GND), U101.52 (GND), U101.53 (GND), U101.54 (GND), U101.55 (GND), U101.56 (GND), U101.57 (GND), U101.58 (GND), U101.59 (GND), U101.60 (GND), U101.61 (GND), U101.62 (GND), U101.63 (GND), U101.64 (GND), U101.65 (GND), U102.3 (GND), U103.32 (EXT_XOSC), U103.33 (GND_EP), U104.3 (GND), U104.7 (EP), Y1.2
unnamed: C104.1, L101.2, R103.1
unnamed: C106.2, C107.1, L103.1
unnamed: C107.2, C113.2, L103.2, L107.1
unnamed: C110.2, L105.2, L106.2
unnamed: C114.1, L107.2, L108.1
unnamed: D101.2 (A), R105.2
unnamed: D102.2 (A), R106.2
unnamed: D103.2 (A), R107.2
unnamed: D104.2 (A), R108.2
unnamed: D105.2 (A), R110.2
unnamed: J102.A5 (CC1), R101.1
unnamed: J102.B5 (CC2), R102.1
unnamed: J104.1 (In), L108.2
unnamed: C116.1, U103.6 (DCPL)
unnamed: C122.1, U103.26 (DCPL_PFD_CHP)
unnamed: C119.1, U103.21 (DCPL_VCO)
unnamed: C125.1, U103.29 (DCPL_XOSC)
unnamed: C112.1, U103.23 (LPF0)
unnamed: C112.2, U103.24 (LPF1)
unnamed: R104.1, U103.14 (RBIAS)
unnamed: C108.1, U103.30 (XOSC_Q1), Y1.1
unnamed: C109.1, U103.31 (XOSC_Q2), Y1.3
